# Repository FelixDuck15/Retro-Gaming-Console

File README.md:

Game console for retro games emulated via Batocera

PCB designed with KiCad 10.0

Case designed with Onshape

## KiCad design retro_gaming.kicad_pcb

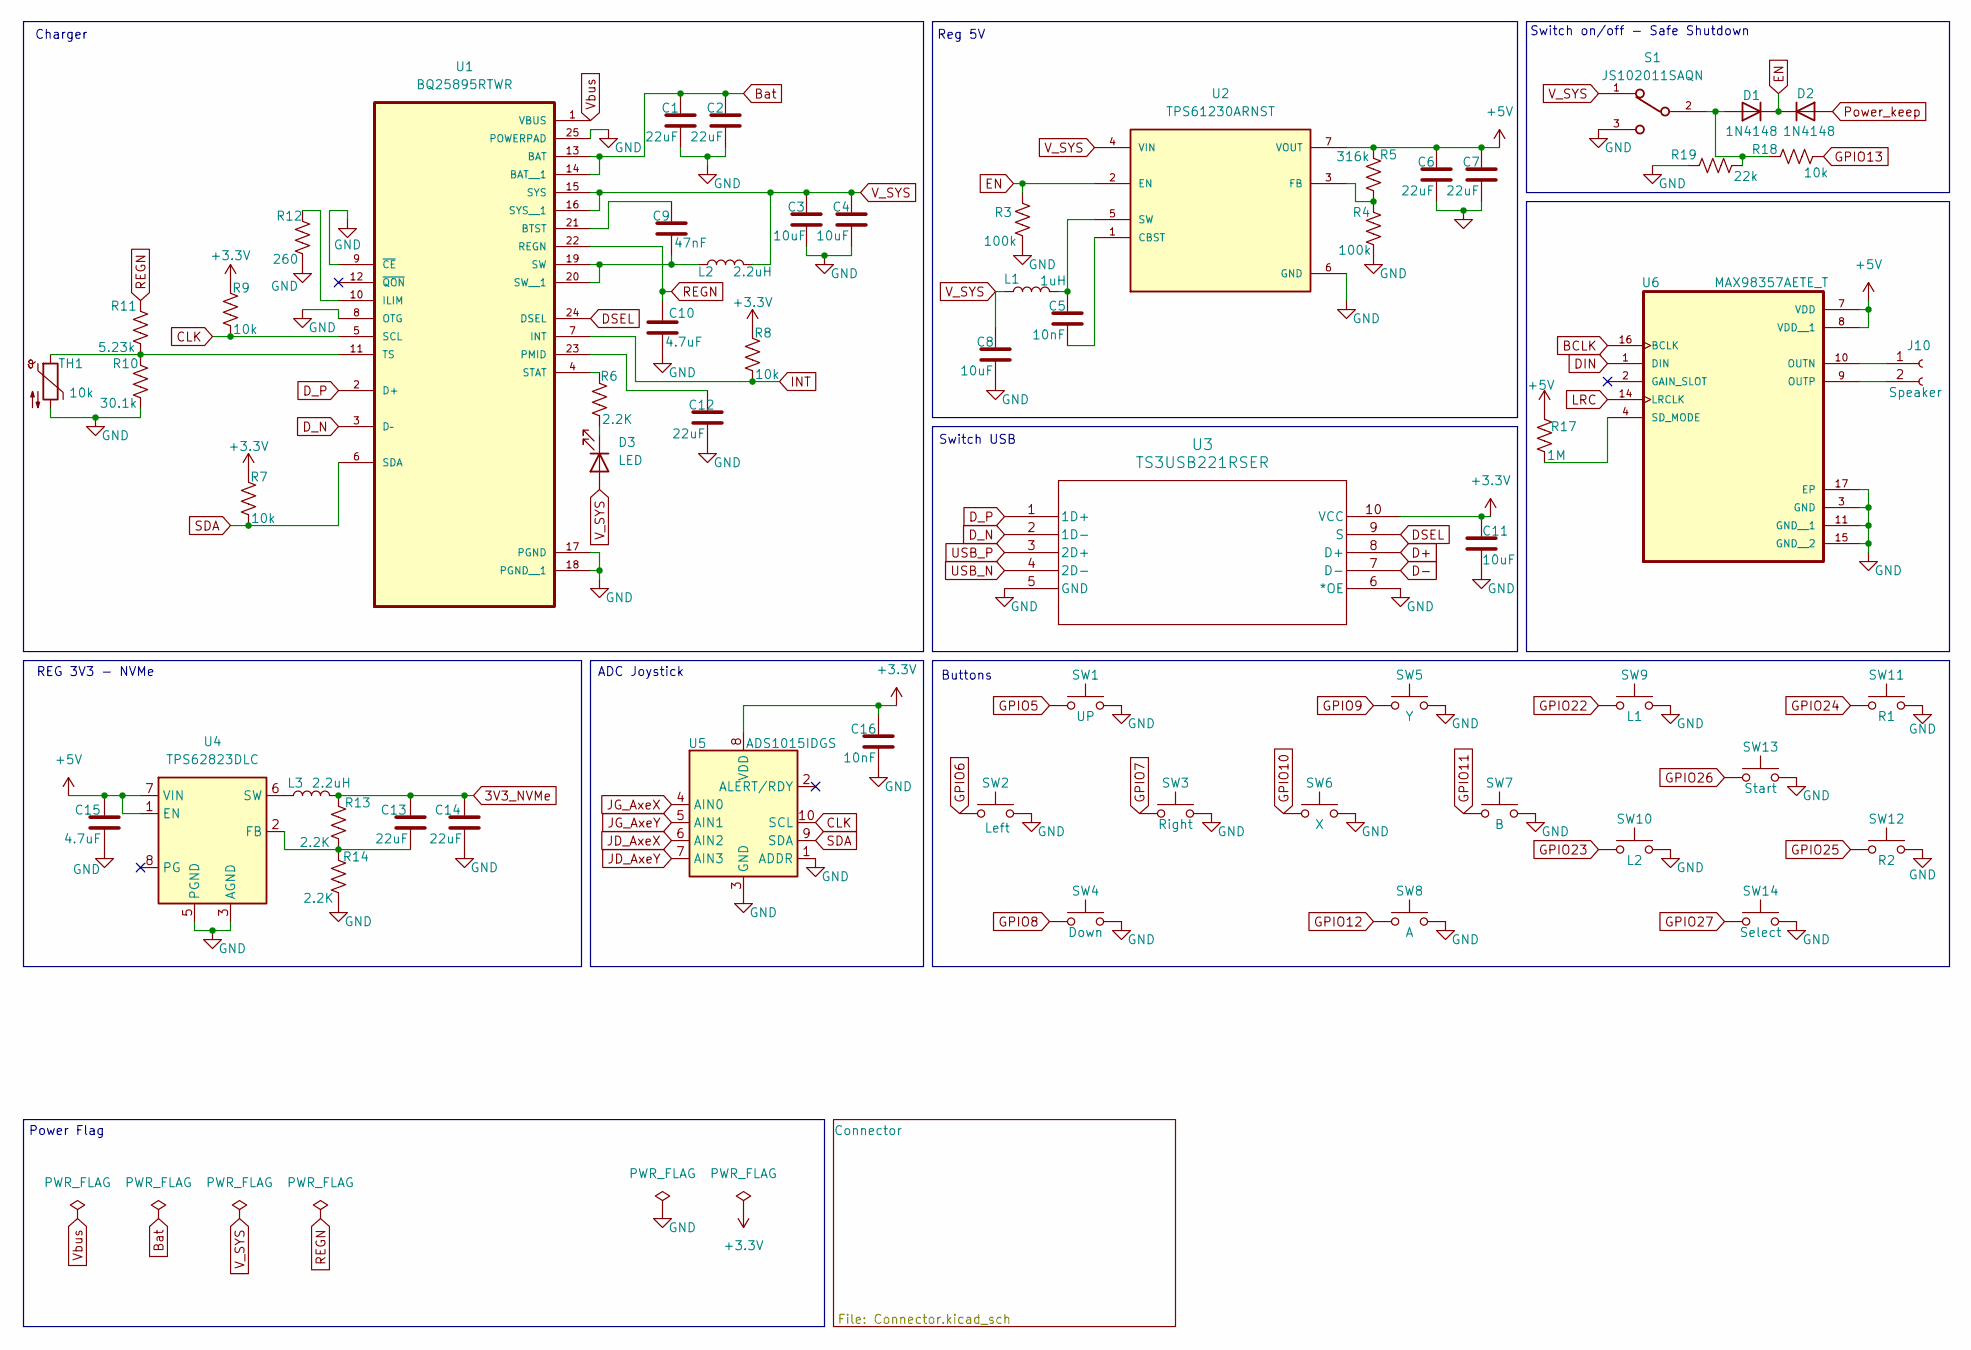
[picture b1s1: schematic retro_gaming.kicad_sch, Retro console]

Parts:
C1, C2, C6, C7, C12, C13, C14: 22uF; C_0805_2012Metric
C3, C4, C8, C11: 10uF; C_0805_2012Metric
C5, C16: 10nF; C_0805_2012Metric
C9: 47nF; C_0805_2012Metric
C10, C15: 4.7uF; C_0805_2012Metric
D1, D2: 1N4148; D_DO-35_SOD27_P7.62mm_Horizontal
D3: LED; LED_0805_2012Metric
J10: Speaker; PinSocket_1x02_P2.00mm_Vertical
L1: 1uH; L_1008_2520Metric
L2, L3: 2.2uH; L_1008_2520Metric
R3, R4: 100k; R_0805_2012Metric
R5: 316k; R_0805_2012Metric
R6, R13, R14: 2.2K; R_0805_2012Metric
R7, R8, R9, R18: 10k; R_0805_2012Metric
R10: 30.1k; R_0805_2012Metric
R11: 5.23k; R_0805_2012Metric
R12: 260; R_0805_2012Metric
R17: 1M; R_0603_1608Metric
R19: 22k; R_0805_2012Metric
S1: JS102011SAQN; SW_JS102011SAQN
SW1: UP; SW_Push_1P1T_NO_CK_KSC6xxG
SW2: Left; SW_Push_1P1T_NO_CK_KSC6xxG
SW3: Right; SW_Push_1P1T_NO_CK_KSC6xxG
SW4: Down; SW_Push_1P1T_NO_CK_KSC6xxG
SW5: Y; SW_Push_1P1T_NO_CK_KSC6xxG
SW6: X; SW_Push_1P1T_NO_CK_KSC6xxG
SW7: B; SW_Push_1P1T_NO_CK_KSC6xxG
SW8: A; SW_Push_1P1T_NO_CK_KSC6xxG
SW9: L1; SW_Push_1P1T_NO_CK_KSC6xxG
SW10: L2; SW_Push_1P1T_NO_CK_KSC6xxG
SW11: R1; SW_Push_1P1T_NO_CK_KSC6xxG
SW12: R2; SW_Push_1P1T_NO_CK_KSC6xxG
SW13: Start; SW_Push_1P1T_NO_CK_KSC6xxG
SW14: Select; SW_Push_1P1T_NO_CK_KSC6xxG
TH1: 10k; R_4020_10251Metric
U1: BQ25895RTWR; QFN50P400X400X80-25N
U2: TPS61230ARNST; IC_TPS61230ARNST; PARTREV B
U3: TS3USB221RSER; RSE10
U4: TPS62823DLC; Texas_VSON-HR-8_1.5x2mm_P0.5mm
U5: ADS1015IDGS; TSSOP-10_3x3mm_P0.5mm
U6: MAX98357AETE_T; QFN50P300X300X80-17N

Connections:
3V3_NVMe: C13.1, C14.1, L3.2, R13.1; also elsewhere on the board
+3.3V: C11.1, C16.1, R7.1, R8.1, R9.1, U3.10 (VCC), U5.8 (VDD); also elsewhere on the board
+5V: C6.1, C7.1, C15.1, R5.1, R17.1, U2.7 (VOUT), U4.1 (EN), U4.7 (VIN), U6.7 (VDD), U6.8 (VDD__1); also elsewhere on the board
BCLK: U6.16 (BCLK); also elsewhere on the board
Bat: C1.1, C2.1, U1.13 (BAT), U1.14 (BAT__1); also elsewhere on the board
CLK: R9.2, U1.5 (SCL), U5.10 (SCL); also elsewhere on the board
D+: U3.8 (D+); also elsewhere on the board
D-: U3.7 (D-); also elsewhere on the board
DIN: U6.1 (DIN); also elsewhere on the board
DSEL: U1.24 (DSEL), U3.9 (S)
D_N: U1.3 (D–), U3.2 (1D-)
D_P: U1.2 (D+), U3.1 (1D+)
EN: D1.1 (K), D2.1 (K), R3.1, U2.2 (EN)
GND: C1.2, C2.2, C3.2, C4.2, C6.2, C7.2, C8.2, C10.2, C11.2, C12.2, C14.2, C15.2, C16.2, R3.2, R4.2, R10.2, R12.2, R14.2, R19.1, S1.3, SW1.2, SW2.2, SW3.2, SW4.2, SW5.2, SW6.2, SW7.2, SW8.2, SW9.2, SW10.2, SW11.2, SW12.2, SW13.2, SW14.2, TH1.2, U1.8 (OTG), U1.9 (~CE), U1.17 (PGND), U1.18 (PGND__1), U1.25 (POWERPAD), U2.6 (GND), U3.5 (GND), U3.6 (*OE), U4.3 (AGND), U4.5 (PGND), U5.1 (ADDR), U5.3 (GND), U6.3 (GND), U6.11 (GND__1), U6.15 (GND__2), U6.17 (EP); also elsewhere on the board
GPIO5: SW1.1; also elsewhere on the board
GPIO6: SW2.1; also elsewhere on the board
GPIO7: SW3.1; also elsewhere on the board
GPIO8: SW4.1; also elsewhere on the board
GPIO9: SW5.1; also elsewhere on the board
GPIO10: SW6.1; also elsewhere on the board
GPIO11: SW7.1; also elsewhere on the board
GPIO12: SW8.1; also elsewhere on the board
GPIO13: R18.2; also elsewhere on the board
GPIO22: SW9.1; also elsewhere on the board
GPIO23: SW10.1; also elsewhere on the board
GPIO24: SW11.1; also elsewhere on the board
GPIO25: SW12.1; also elsewhere on the board
GPIO26: SW13.1; also elsewhere on the board
GPIO27: SW14.1; also elsewhere on the board
INT: R8.2, U1.7 (INT); also elsewhere on the board
JD_AxeX: U5.6 (AIN2); also elsewhere on the board
JD_AxeY: U5.7 (AIN3); also elsewhere on the board
JG_AxeX: U5.4 (AIN0); also elsewhere on the board
JG_AxeY: U5.5 (AIN1); also elsewhere on the board
LRC: U6.14 (LRCLK); also elsewhere on the board
unnamed: D1.2 (A), R18.1, R19.2, S1.2
unnamed: D3.1 (K), R6.2
unnamed: J10.1, U6.10 (OUTN)
unnamed: J10.2, U6.9 (OUTP)
unnamed: C9.1, U1.21 (BTST)
unnamed: R12.1, U1.10 (ILIM)
unnamed: C12.1, U1.23 (PMID)
unnamed: R6.1, U1.4 (STAT)
unnamed: C9.2, L2.1, U1.19 (SW), U1.20 (SW__1)
unnamed: R10.1, R11.2, TH1.1, U1.11 (TS)
unnamed: C5.2, U2.1 (CBST)
unnamed: R4.1, R5.2, U2.3 (FB)
unnamed: C5.1, L1.2, U2.5 (SW)
unnamed: C13.2, R13.2, R14.1, U4.2 (FB)
unnamed: L3.1, U4.6 (SW)
unnamed: R17.2, U6.4 (SD_MODE)
Power_keep: D2.2 (A); also elsewhere on the board
REGN: C10.1, R11.1, U1.22 (REGN)
SDA: R7.2, U1.6 (SDA), U5.9 (SDA); also elsewhere on the board
USB_N: U3.4 (2D-); also elsewhere on the board
USB_P: U3.3 (2D+); also elsewhere on the board
V_SYS: C3.1, C4.1, C8.1, D3.2 (A), L1.1, L2.2, S1.1, U1.15 (SYS), U1.16 (SYS__1), U2.4 (VIN)
Vbus: U1.1 (VBUS); also elsewhere on the board

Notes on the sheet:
Switch USB
ADC Joystick
Charger
Reg 5V
Buttons
REG 3V3 - NVMe
Power Flag
Switch on/off - Safe Shutdown

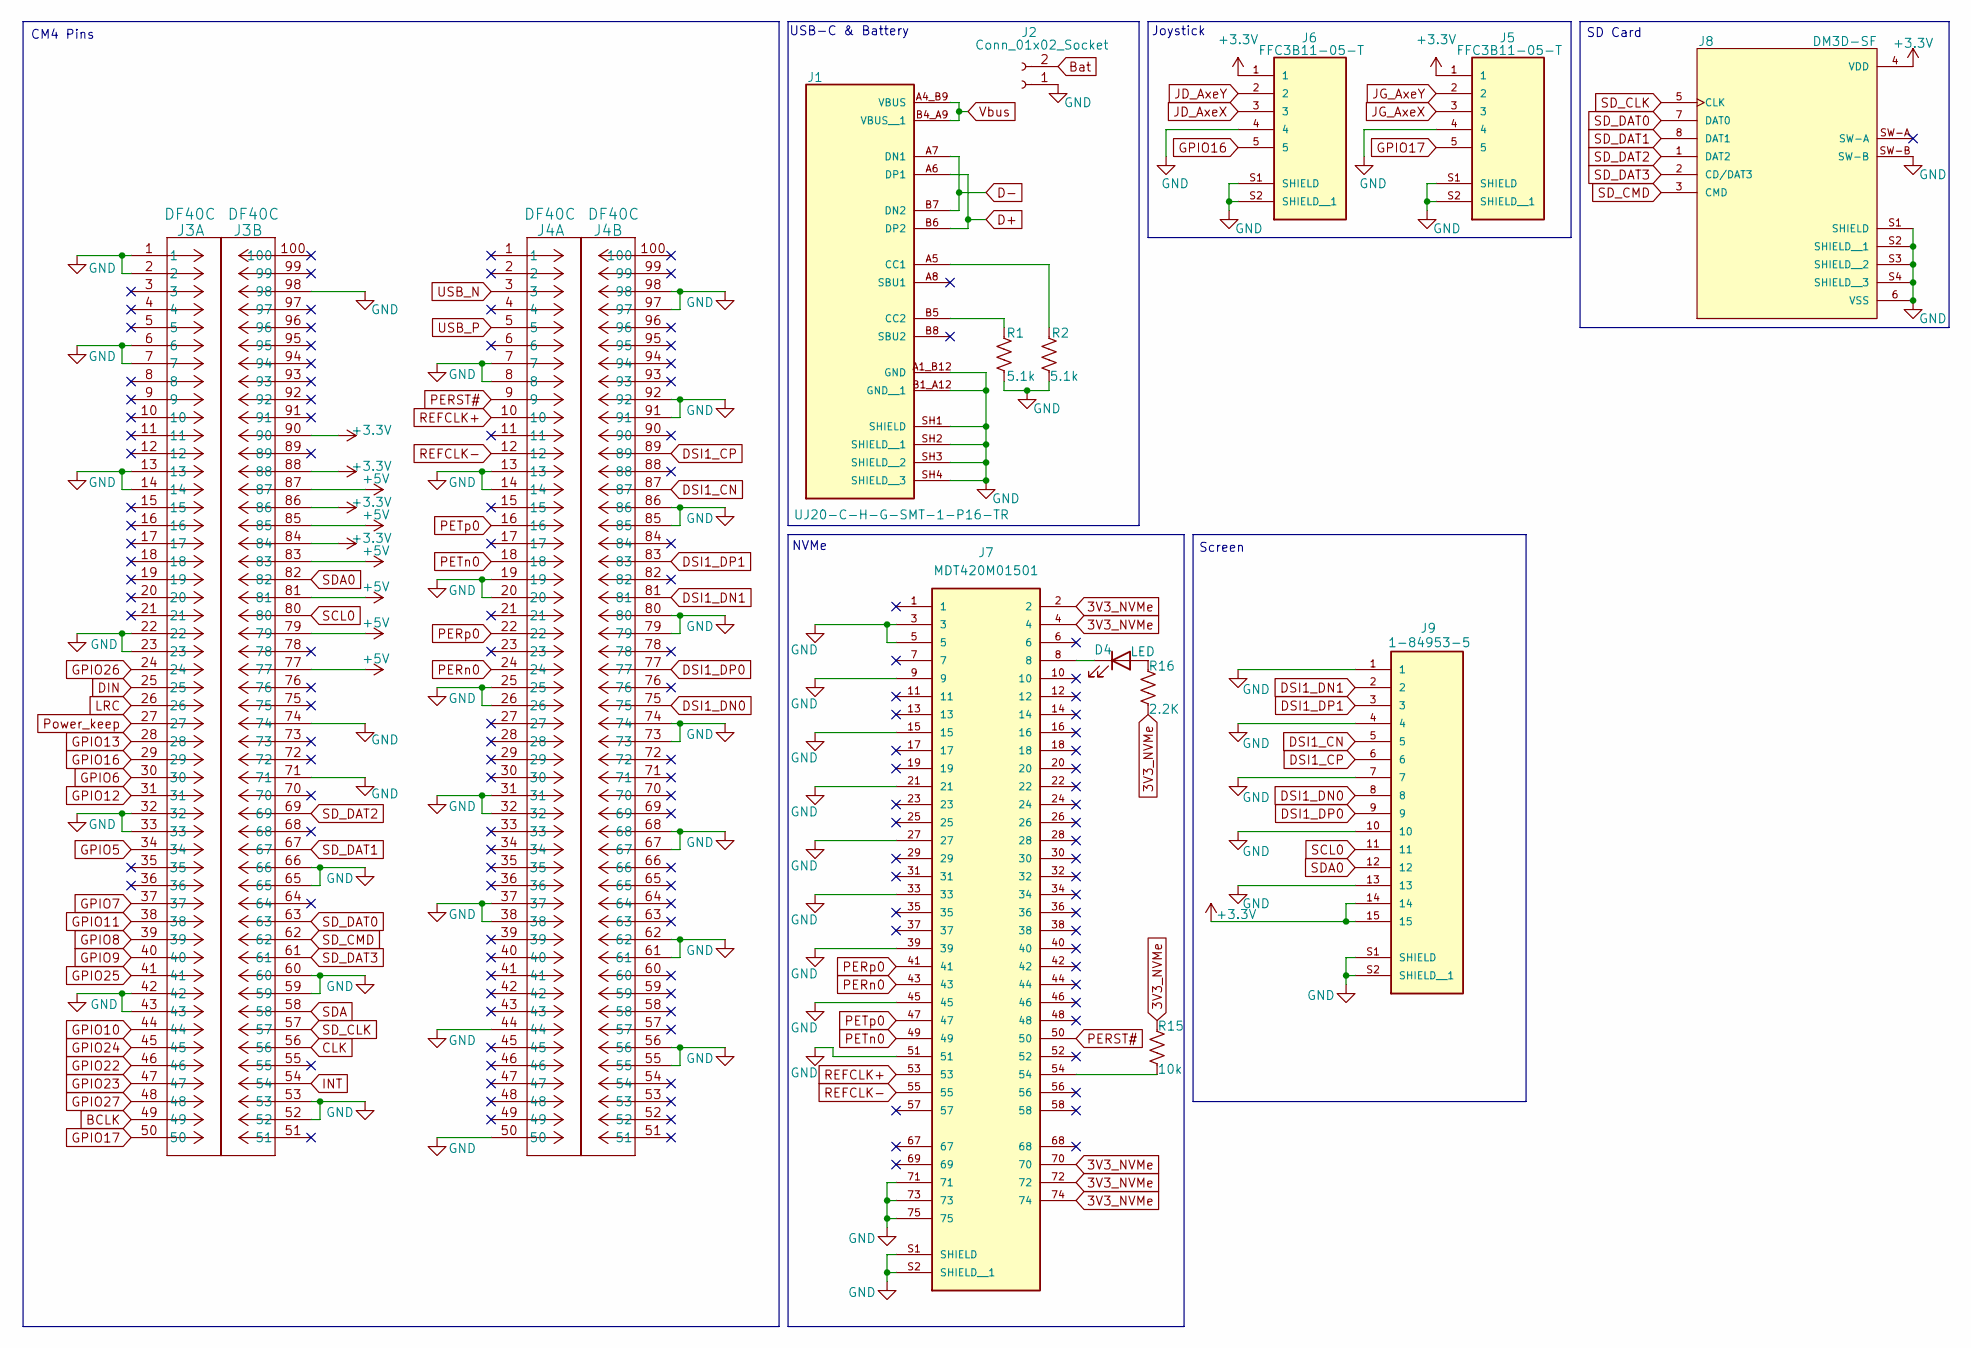
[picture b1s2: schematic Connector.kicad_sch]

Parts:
D4: LED; LED_0805_2012Metric
J1: UJ20-C-H-G-SMT-1-P16-TR; SAMESKY_UJ20-C-H-G-SMT-1-P16-TR; PARTREV 1.0
J2: Conn_01x02_Socket; PinSocket_1x02_P2.00mm_Vertical
J3, J4: DF40C; CONN_DF40C-100DS-0.4V58_HIR
J5, J6: FFC3B11-05-T; GCT_FFC3B11-05-T; PARTREV A
J7: MDT420M01501; AMPHENOL_MDT420M01501; PARTREV A
J8: DM3D-SF; HRS_DM3D-SF; PARTREV 2017.1
J9: 1-84953-5; TE_1-84953-5; PARTREV A4
R1, R2: 5.1k; R_0805_2012Metric
R15: 10k; R_0805_2012Metric
R16: 2.2K; R_0805_2012Metric

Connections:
3V3_NVMe: J7.2, J7.4, J7.70, J7.72, J7.74, R15.1, R16.2; also elsewhere on the board
+3.3V: J3.84, J3.86, J3.88, J3.90, J5.1, J6.1, J8.4 (VDD), J9.14, J9.15; also elsewhere on the board
+5V: J3.77, J3.79, J3.81, J3.83, J3.85, J3.87; also elsewhere on the board
BCLK: J3.49; also elsewhere on the board
Bat: J2.2; also elsewhere on the board
CLK: J3.56; also elsewhere on the board
D+: J1.A6 (DP1), J1.B6 (DP2); also elsewhere on the board
D-: J1.A7 (DN1), J1.B7 (DN2); also elsewhere on the board
DIN: J3.25; also elsewhere on the board
DSI1_CN: J4.87, J9.5
DSI1_CP: J4.89, J9.6
DSI1_DN0: J4.75, J9.8
DSI1_DN1: J4.81, J9.2
DSI1_DP0: J4.77, J9.9
DSI1_DP1: J4.83, J9.3
GND: J1.A1_B12 (GND), J1.B1_A12 (GND__1), J1.SH1 (SHIELD), J1.SH2 (SHIELD__1), J1.SH3 (SHIELD__2), J1.SH4 (SHIELD__3), J2.1, J3.1, J3.2, J3.6, J3.7, J3.13, J3.14, J3.22, J3.23, J3.32, J3.33, J3.42, J3.43, J3.52, J3.53, J3.59, J3.60, J3.65, J3.66, J3.71, J3.74, J3.98, J4.7, J4.8, J4.13, J4.14, J4.19, J4.20, J4.25, J4.26, J4.31, J4.32, J4.37, J4.38, J4.44, J4.50, J4.55, J4.56, J4.61, J4.62, J4.67, J4.68, J4.73, J4.74, J4.79, J4.80, J4.85, J4.86, J4.91, J4.92, J4.97, J4.98, J5.4, J5.S1 (SHIELD), J5.S2 (SHIELD__1), J6.4, J6.S1 (SHIELD), J6.S2 (SHIELD__1), J7.3, J7.5, J7.9, J7.15, J7.21, J7.27, J7.33, J7.39, J7.45, J7.51, J7.71, J7.73, J7.75, J7.S1 (SHIELD), J7.S2 (SHIELD__1), J8.6 (VSS), J8.S1 (SHIELD), J8.S2 (SHIELD__1), J8.S3 (SHIELD__2), J8.S4 (SHIELD__3), J8.SW-B, J9.1, J9.4, J9.7, J9.10, J9.13, J9.S1 (SHIELD), J9.S2 (SHIELD__1), R1.2, R2.2; also elsewhere on the board
GPIO5: J3.34; also elsewhere on the board
GPIO6: J3.30; also elsewhere on the board
GPIO7: J3.37; also elsewhere on the board
GPIO8: J3.39; also elsewhere on the board
GPIO9: J3.40; also elsewhere on the board
GPIO10: J3.44; also elsewhere on the board
GPIO11: J3.38; also elsewhere on the board
GPIO12: J3.31; also elsewhere on the board
GPIO13: J3.28; also elsewhere on the board
GPIO16: J3.29, J6.5
GPIO17: J3.50, J5.5
GPIO22: J3.46; also elsewhere on the board
GPIO23: J3.47; also elsewhere on the board
GPIO24: J3.45; also elsewhere on the board
GPIO25: J3.41; also elsewhere on the board
GPIO26: J3.24; also elsewhere on the board
GPIO27: J3.48; also elsewhere on the board
INT: J3.54; also elsewhere on the board
JD_AxeX: J6.3; also elsewhere on the board
JD_AxeY: J6.2; also elsewhere on the board
JG_AxeX: J5.3; also elsewhere on the board
JG_AxeY: J5.2; also elsewhere on the board
LRC: J3.26; also elsewhere on the board
unnamed: D4.2 (A), R16.1
unnamed: D4.1 (K), J7.8
unnamed: J1.A5 (CC1), R2.1
unnamed: J1.B5 (CC2), R1.1
unnamed: J7.54, R15.2
PERST#: J4.9, J7.50
PERn0: J4.24, J7.43
PERp0: J4.22, J7.41
PETn0: J4.18, J7.49
PETp0: J4.16, J7.47
Power_keep: J3.27; also elsewhere on the board
REFCLK+: J4.10, J7.53
REFCLK-: J4.12, J7.55
SCL0: J3.80, J9.11
SDA: J3.58; also elsewhere on the board
SDA0: J3.82, J9.12
SD_CLK: J3.57, J8.5 (CLK)
SD_CMD: J3.62, J8.3 (CMD)
SD_DAT0: J3.63, J8.7 (DAT0)
SD_DAT1: J3.67, J8.8 (DAT1)
SD_DAT2: J3.69, J8.1 (DAT2)
SD_DAT3: J3.61, J8.2 (CD/DAT3)
USB_N: J4.3; also elsewhere on the board
USB_P: J4.5; also elsewhere on the board
Vbus: J1.A4_B9 (VBUS), J1.B4_A9 (VBUS__1); also elsewhere on the board

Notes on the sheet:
USB-C & Battery
Joystick
SD Card
Screen
CM4 Pins
NVMe

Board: 2 copper layers, 74 parts (0 on the bottom side), 86 nets, no tracks yet.
